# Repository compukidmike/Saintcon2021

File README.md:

# Saintcon2021

This year's badge was created by compukidmike, Professor_Plum, and Sodium_Hydrogen. It's styled after a combination lock and the shackle actually opens!

We tried something different for the front PCB. We used pcbbuy.com because they can do 2-color soldermask. It didn't turn out exactly like planned, but it was still a cool option that we'll probably use in the future.

One of the major features of the badge is NFC. The badge can read and write NFC tags, as well as emulate cards. This is used for sharing contact information, reading unlock tags, and trading items.

The main microcontroller is an ATSAME53J18A. The NFC controller is an ST25R95 and the LCD is actually round. The badge is composed of a stack of PCBs (4 boards thick, 5 boards total). Here's an exploded view of the badge:

One of the big challenges was fitting parts under the screen. We've got the thickness of 2 boards (3.2mm) to fit everything. The LCD is 2.2mm thick, so that leaves 1mm for components. This made it extremely difficult to find parts, especially with the chip shortages this year.

## Firmware

### Compiling

You'll need to install ~~Atmel~~ Microchip Studio to compile the firmware. Once it's compiled, you can flash it to the badge with an SWD programmer, or follow the directions below to use the USB bootloader.

### Making a UF2 File

When you've compiled the firmware, Microchip Studio will create a bunch of files (likely in the Debug folder inside your project folder). You want the .hex file. You'll need to use a tool called uf2conv.py from https://github.com/microsoft/uf2 (it's in the utils folder). This python script will convert your hex file into a UF2 file that you can use to program your badge. Here's an example command: python .\uf2conv.py .\flash.bin -c -o .\flash.uf2

### Flashing

To re-flash your badge there is a USB bootloader. To activate it, move the power switch to USB and hold the button on the right side of the badge when you connect it to your computer. The screen should show some hardware tests and then it will connect to your computer as a mass storage device. Simply copy the new UF2 firmware file to the badge.

### External SPI Flash

The badge has an 8MB SPI flash chip that stores all the images. It can be reprogrammed via the bootloader, but it's a bit cumbersome. You'll need to use the makeFlash.py script in the ExternalFlash folder to create a binary file from the images. NOTE: The images will be placed in the binary one after the other aligned to 1024 byte boundaries. If you change the images, you'll need to update the list of image locations in flash.h

Once you've got the binary file, you need to convert it to a hex file. This can be done with with bin2hex.py script in the ExternalFlash folder. Here's an example command: python .\bin2hex.py .\flash.bin .\flash.hex

Finally, you need to convert this hex file into a UF2 file that the bootloader can use to reprogram the SPI flash. When using the uf2conv.py script, you'll need to add an offset parameter so that the bootloader knows this data is for the SPI flash. Here's an example command: python .\uf2conv.py .\flash.bin -c -b 0x4000000 -o .\flash.uf2

NOTE: When copying a UF2 file that reprograms the SPI flash, the badge will send an erase command to the SPI flash. This can take a while (30-60 seconds) and you will see an activity indicator on the screen. If this process takes too long, your computer may timeout on copying the file (the badge will change from "erasing" to "writing", but the LED will be pulsing slowly instead of blinking rapidly). If this happens, simply reset the badge into bootloader mode and copy the file again. This time the SPI flash will be empty and the erase command will be quick.

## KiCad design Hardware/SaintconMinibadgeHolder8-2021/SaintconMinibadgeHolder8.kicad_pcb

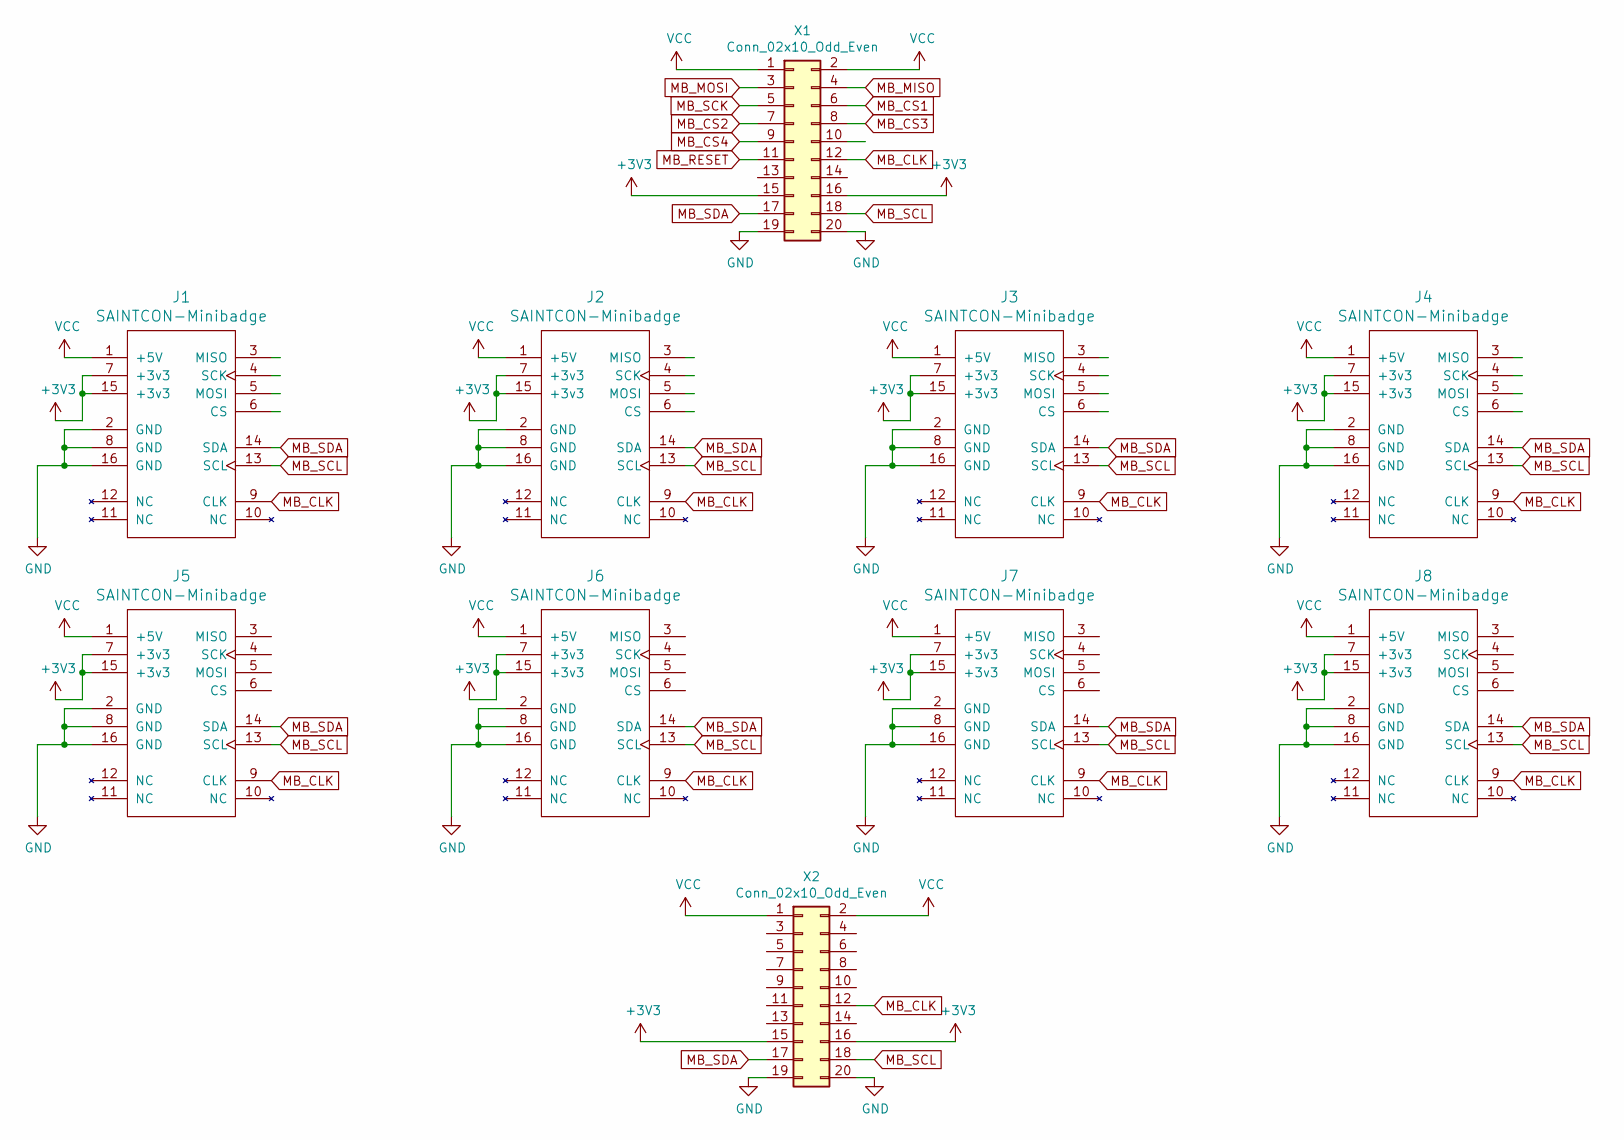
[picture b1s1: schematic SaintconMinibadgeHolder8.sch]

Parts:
J1, J2, J3, J4, J5, J6, J7, J8: SAINTCON-Minibadge; SAINTCON-Minibadge-Shiny
X1, X2: Conn_02x10_Odd_Even; Pin_Header_Straight_2x10_Pitch2.54mm

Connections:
+3V3: J1.7 (+3v3), J1.15 (+3v3), J2.7 (+3v3), J2.15 (+3v3), J3.7 (+3v3), J3.15 (+3v3), J4.7 (+3v3), J4.15 (+3v3), J5.7 (+3v3), J5.15 (+3v3), J6.7 (+3v3), J6.15 (+3v3), J7.7 (+3v3), J7.15 (+3v3), J8.7 (+3v3), J8.15 (+3v3), X1.15, X1.16, X2.15, X2.16
GND: J1.2 (GND), J1.8 (GND), J1.16 (GND), J2.2 (GND), J2.8 (GND), J2.16 (GND), J3.2 (GND), J3.8 (GND), J3.16 (GND), J4.2 (GND), J4.8 (GND), J4.16 (GND), J5.2 (GND), J5.8 (GND), J5.16 (GND), J6.2 (GND), J6.8 (GND), J6.16 (GND), J7.2 (GND), J7.8 (GND), J7.16 (GND), J8.2 (GND), J8.8 (GND), J8.16 (GND), X1.19, X1.20, X2.19, X2.20
MB_CLK: J1.9 (CLK), J2.9 (CLK), J3.9 (CLK), J4.9 (CLK), J5.9 (CLK), J6.9 (CLK), J7.9 (CLK), J8.9 (CLK), X1.12, X2.12
MB_CS1: X1.6
MB_CS2: X1.7
MB_CS3: X1.8
MB_CS4: X1.9
MB_MISO: X1.4
MB_MOSI: X1.3
MB_RESET: X1.11
MB_SCK: X1.5
MB_SCL: J1.13 (SCL), J2.13 (SCL), J3.13 (SCL), J4.13 (SCL), J5.13 (SCL), J6.13 (SCL), J7.13 (SCL), J8.13 (SCL), X1.18, X2.18
MB_SDA: J1.14 (SDA), J2.14 (SDA), J3.14 (SDA), J4.14 (SDA), J5.14 (SDA), J6.14 (SDA), J7.14 (SDA), J8.14 (SDA), X1.17, X2.17
VCC: J1.1 (+5V), J2.1 (+5V), J3.1 (+5V), J4.1 (+5V), J5.1 (+5V), J6.1 (+5V), J7.1 (+5V), J8.1 (+5V), X1.1, X1.2, X2.1, X2.2

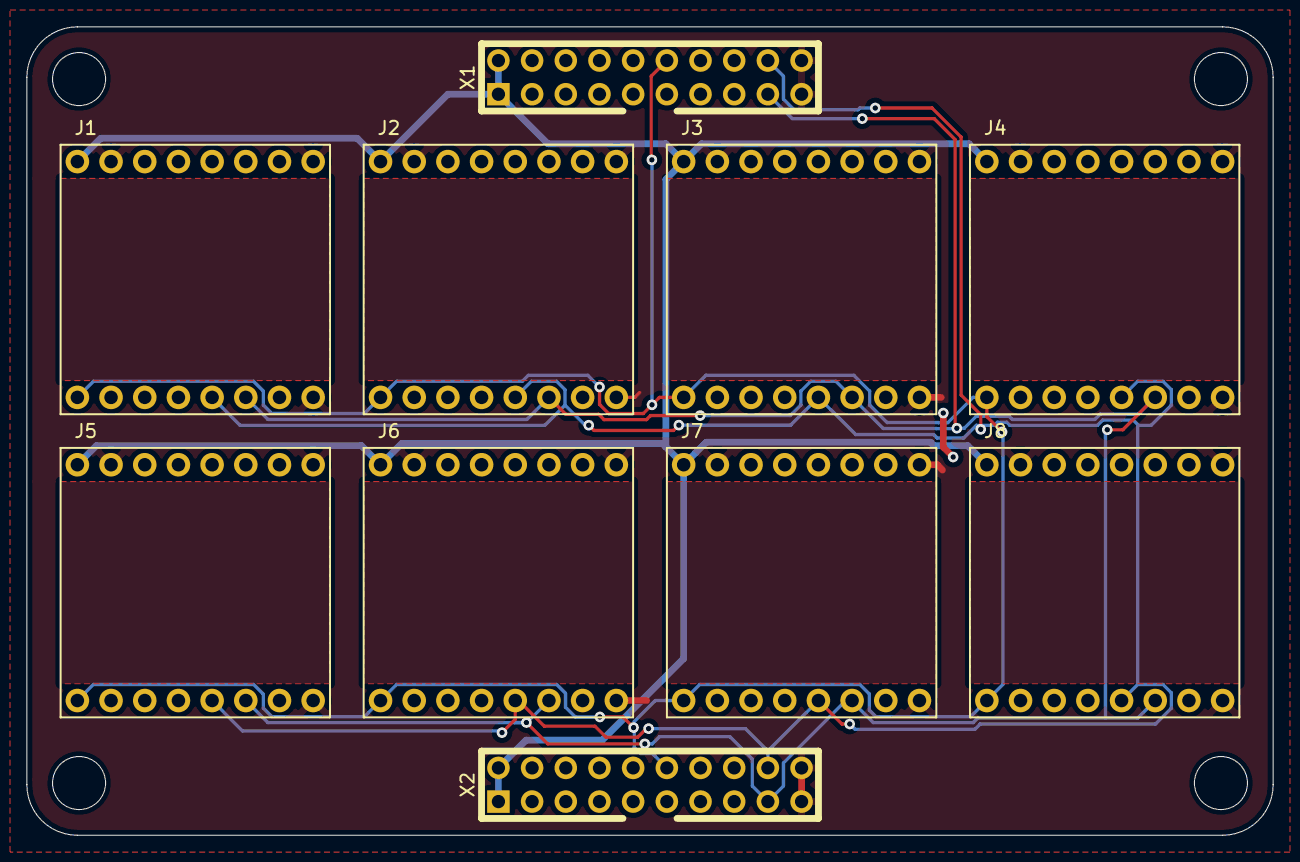
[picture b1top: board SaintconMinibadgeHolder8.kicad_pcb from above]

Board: 2 copper layers, 94.0 x 61.0 mm, 11 parts (1 on the bottom side), 6 nets.

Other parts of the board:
Ref**: Val**; SaintconLogo2021

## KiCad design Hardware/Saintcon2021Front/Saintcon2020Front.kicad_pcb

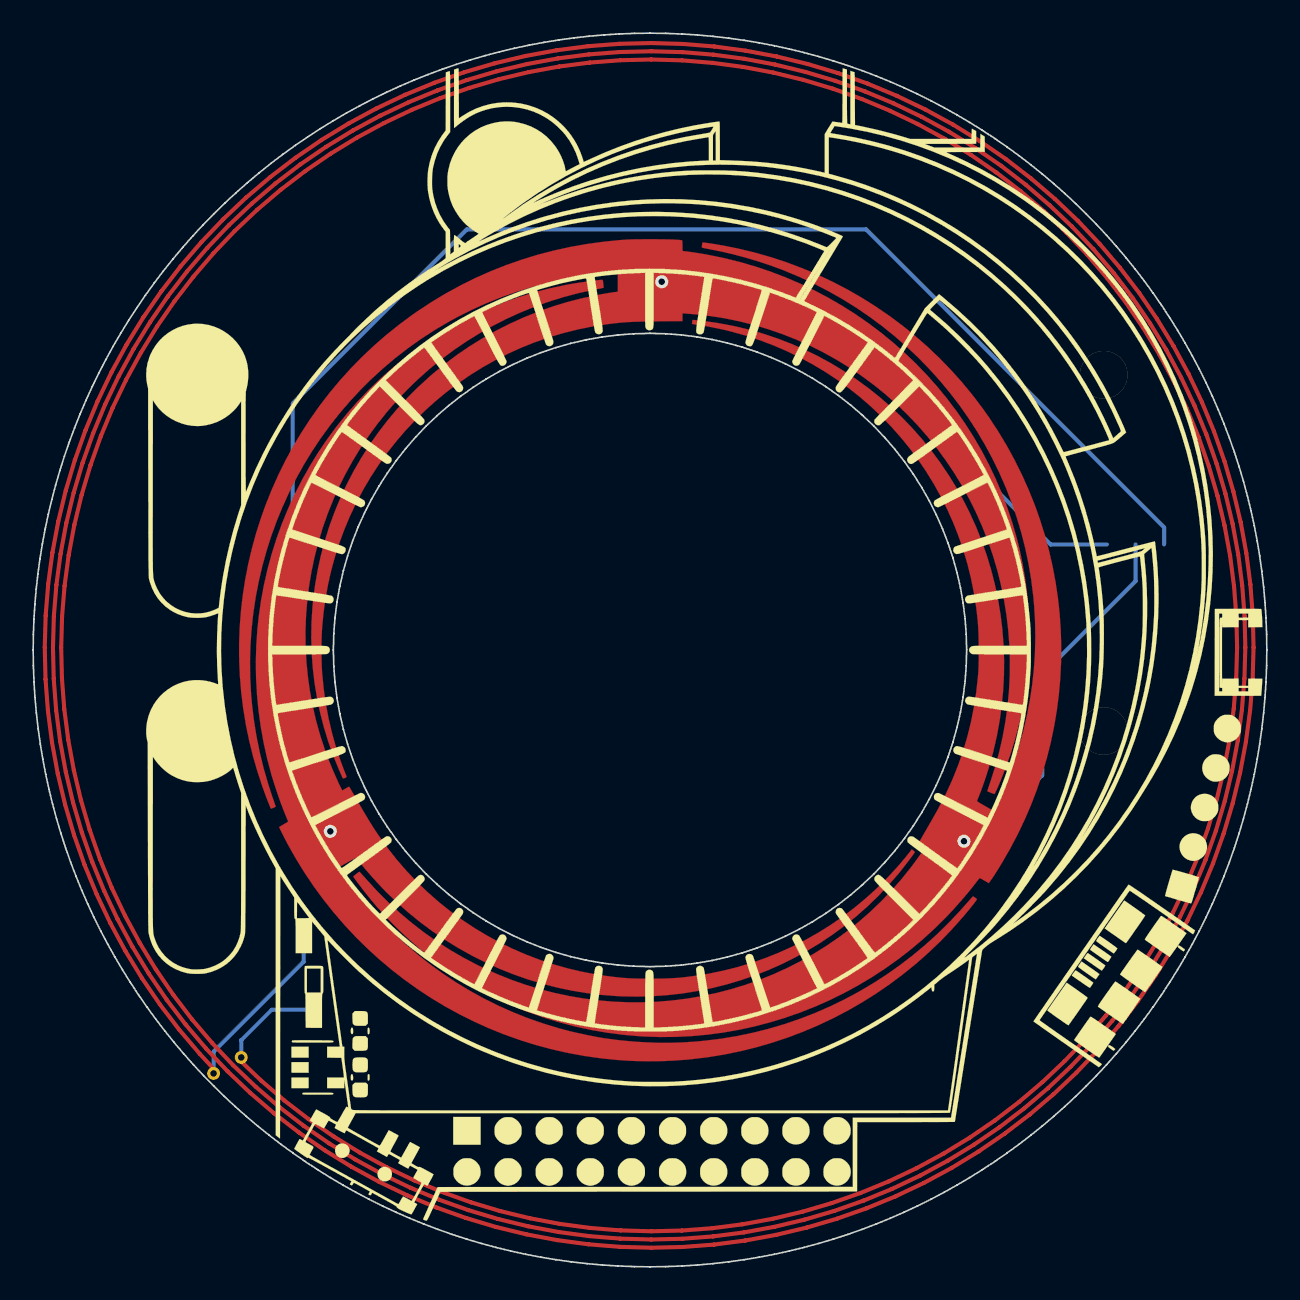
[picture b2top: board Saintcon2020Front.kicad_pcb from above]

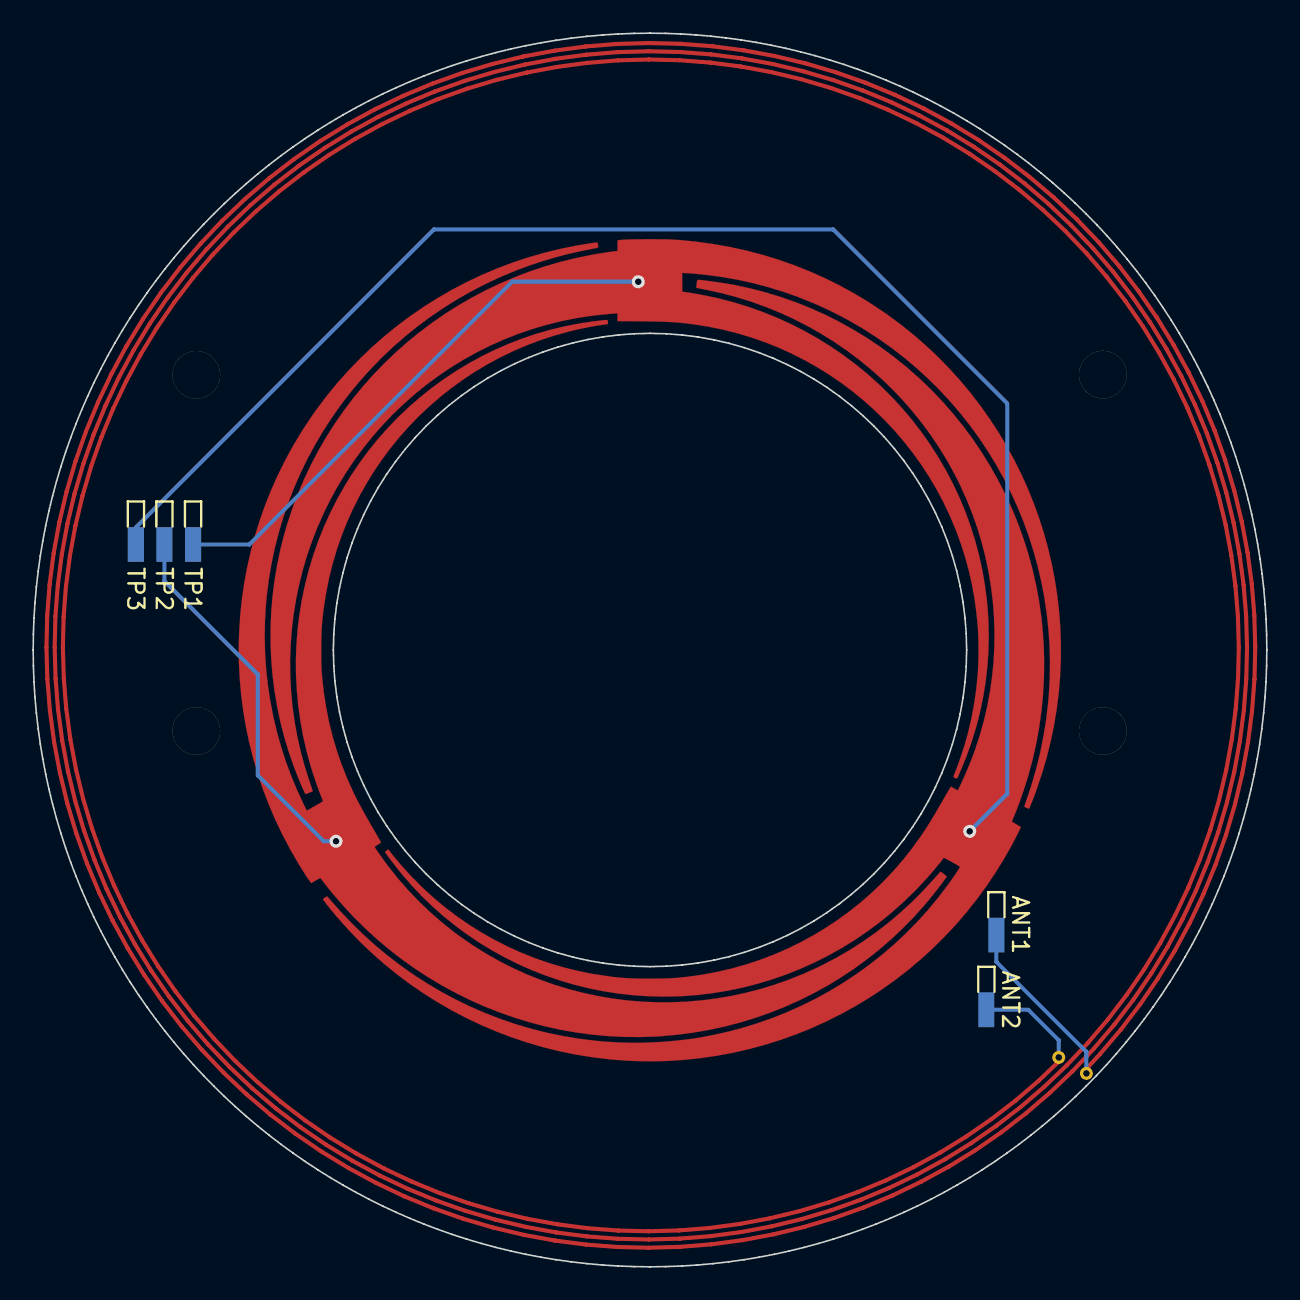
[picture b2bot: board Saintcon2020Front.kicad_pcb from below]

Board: 2 copper layers, 76.2 x 76.2 mm, 7 parts (5 on the bottom side), 2 nets.

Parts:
AE1: Antenna_Loop; SpiralAnt3_254000_508000
ANT1, ANT2: TestPoint; SPRING-120220-0315
Ref**: Val**; BoardFront3-Yellow
TP1, TP2, TP3: TestPoint; SPRING-120220-0315

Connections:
unnamed: AE1.1, ANT2.1
unnamed: AE1.2, ANT1.1

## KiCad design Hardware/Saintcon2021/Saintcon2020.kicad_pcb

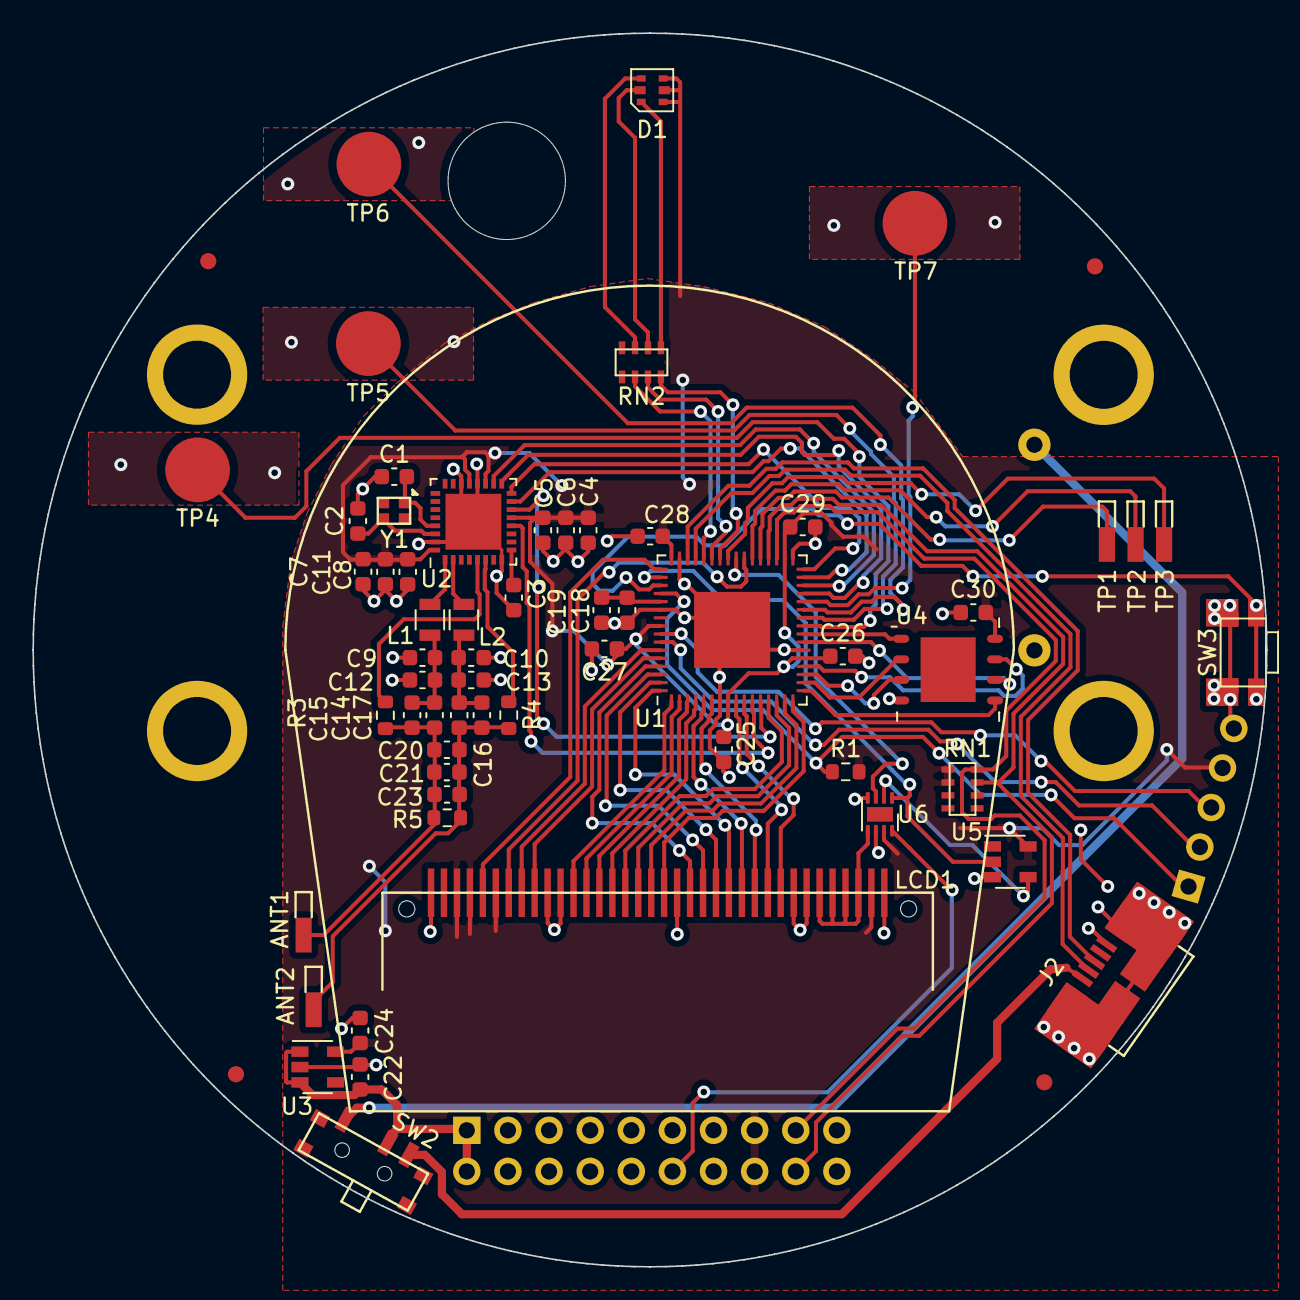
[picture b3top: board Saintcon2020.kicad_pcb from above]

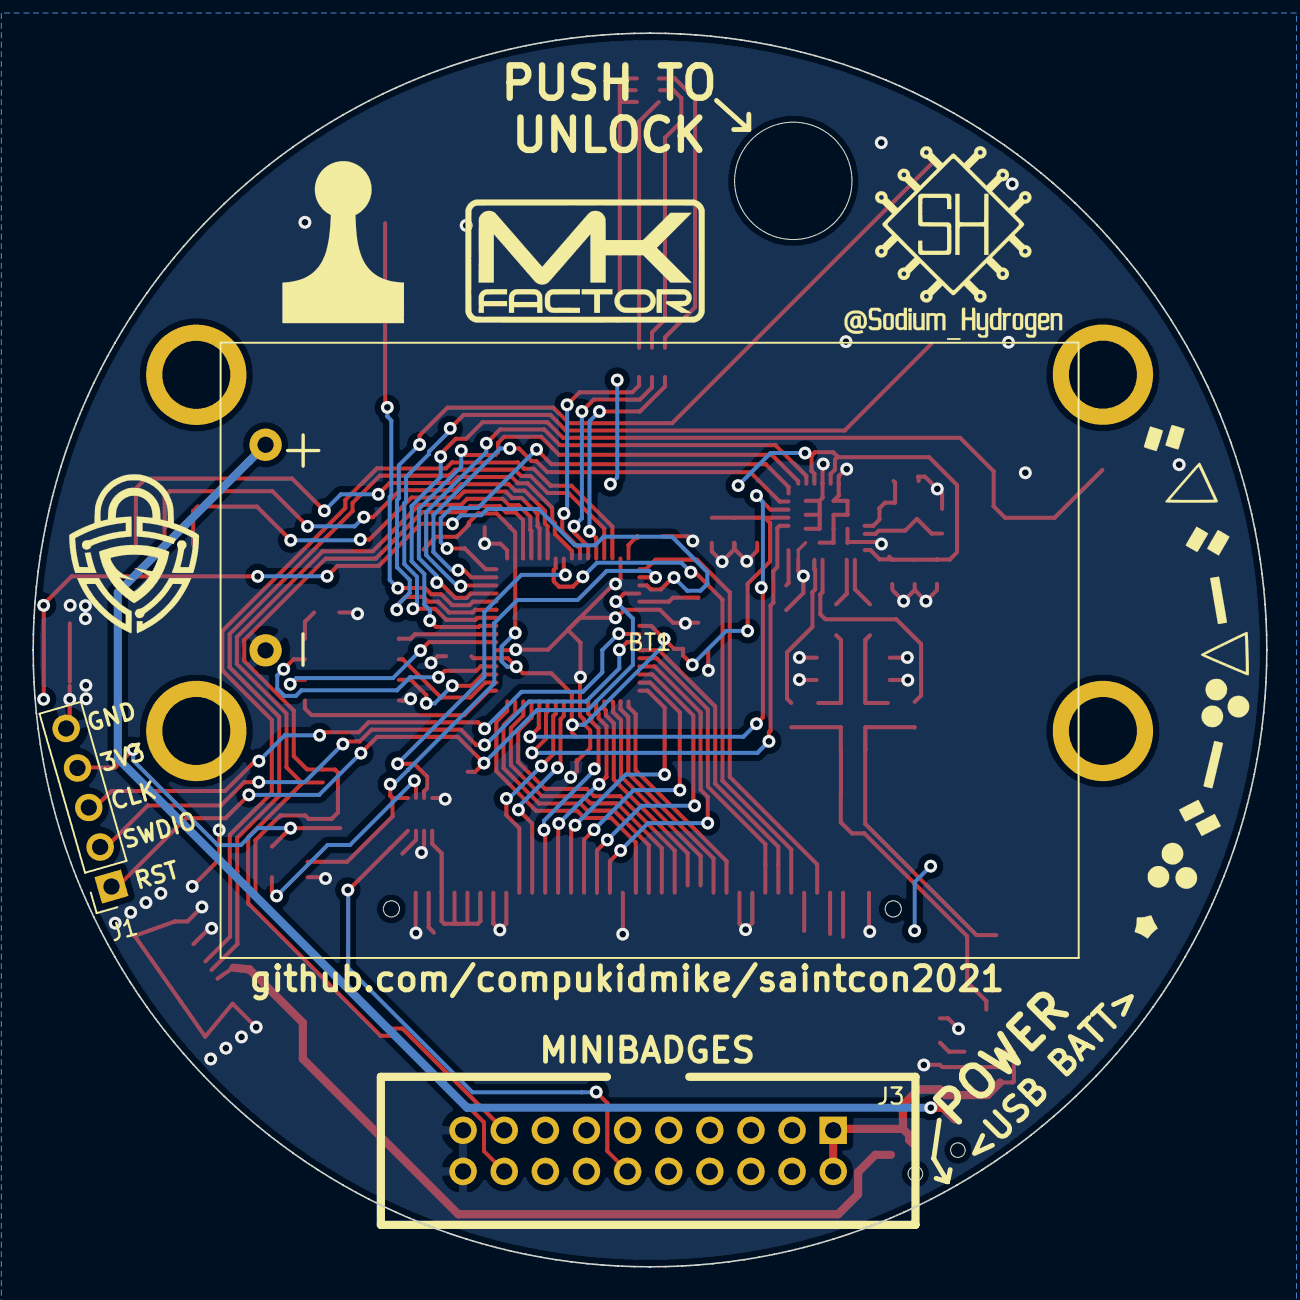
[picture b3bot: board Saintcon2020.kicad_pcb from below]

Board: 2 copper layers, 76.2 x 76.2 mm, 75 parts (6 on the bottom side), 75 nets.

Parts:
ANT1: NFC_ANT1; SPRING-120220-0315
ANT2: NFC_ANT2; SPRING-120220-0315
BT1: Battery; Battery3xAAA
C1, C2, C15, C16: 10pF; C_0603_1608Metric
C3: 1nF; C_0603_1608Metric
C4, C7: 1uF; C_0603_1608Metric
C5, C8: 0.01uF; C_0603_1608Metric
C6, C11, C18, C25, C26, C27, C28, C29, C30: 0.1uF; C_0603_1608Metric
C9, C10, C12, C13: 100pF; C_0603_1608Metric
C14, C17: 47pF; C_0603_1608Metric
C19, C22, C24: 4.7uF; C_0603_1608Metric
C20: 24pF; C_0603_1608Metric
C21, C23: DNP; C_0603_1608Metric
D1: 19-337C/RSBHGHC-A88/4T; 19-337C_RSBHGHC-A88_4T
FID1, FID2, FID3, FID4: Fiducial_1mm_Mask2mm
J1: Conn_01x05; PinSocket_1x05_P2.54mm_Vertical
J2: USB_B_Micro; 10118192-0002LF
J3: SBH11-PBPC-D10-ST-BK; Pin_Header_Straight_2x10_Pitch2.54mm
L1, L2: 560nH; L_0805
LCD1: RoundLCD; RoundLCD-36P
R1: 10k; R_0603_1608Metric
R3, R4: 330; R_0603_1608Metric
R5: DNP; R_0603_1608Metric
RN1, RN2: 1K; RAVF164D-RES_PACK_4
Ref**: Val**; SodiumHydrogen_logo
Ref**#2: Val**; SaintconLogo2021
Ref**#3: Val**; BackSilkCombo
Ref**#4: Val**; ProfessorPlum_logo
Ref**#5: Val**; BoardShape
STANDOFF1, STANDOFF2, STANDOFF3, STANDOFF4: Standoff-4-40
SW2: SW_SPDT; CUS-12B
SW3: SELECT; KMS231GFLS
TP1, TP2, TP3: TOUCH; SPRING-120220-0315
TP4, TP5, TP6: SHACKLE; TouchButton4mm
TP7: SHIM; TouchButton4mm
U1: ATSAME53J18A-M; QFN-64-1EP_9x9mm_P0.5mm_EP4.7x4.7mm
U2: ST25R95
U3: NCP115ASN330T2G; SOT-23-5
U4: AT25QF641B-MHB-T; UDFN-8_EP_6x5_Pitch1.27mm
U5: SN74LVC1G04DBVRG4; SOT-23-5
U6: A3910; DFN-8-1EP_2x2mm_P0.5mm_EP0.9x1.6mm
Y1: XRCGB27M120F3M10R0; Crystal-XRCGB27M120F3M10R0

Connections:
+3V3: C4.2, C5.2, C6.2, C7.2, C8.2, C11.2, C24.1, C25.1, C26.1, C27.1, C28.1, C29.1, C30.2, D1.2, D1.4, D1.6, J1.4, J3.15, J3.16, LCD1.2, LCD1.31, LCD1.33, LCD1.34, R1.2, RN1.7, RN1.8, U1.8, U1.21, U1.34, U1.48, U1.56, U2.13, U2.19, U2.21, U2.32, U3.5, U4.8, U5.5, U6.7
/D1: LCD1.25, U1.1
/D2: LCD1.24, U1.2
/D3: LCD1.23, U1.3
/D4: LCD1.22, U1.4
/D5: LCD1.21, U1.13
/D6: LCD1.20, U1.14
/D7: LCD1.19, U1.15
/D8: LCD1.18, U1.16
/D10: LCD1.16, U1.61
/D11: LCD1.15, U1.62
/D12: LCD1.14, U1.63
/D13: LCD1.13, U1.64
/D14: LCD1.12, U1.5
/D15: LCD1.11, U1.6
/D16: LCD1.10, U1.9
/D17: LCD1.9, U1.10
D+: J2.3, U1.46
D-: J2.2, U1.45
GND: BT1.2, C1.2, C2.2, C3.1, C4.1, C5.1, C6.1, C7.1, C8.1, C9.2, C10.1, C11.1, C12.2, C13.1, C18.2, C19.2, C22.2, C24.2, C25.2, C26.2, C27.2, C28.2, C29.2, C30.1, J1.5, J2.5, J2.6, J3.19, J3.20, LCD1.1, LCD1.7, LCD1.8, LCD1.17, LCD1.26, LCD1.27, LCD1.36, SW3.1, U1.7, U1.22, U1.33, U1.47, U1.54, U1.65, U2.8, U2.20, U2.22, U2.31, U2.33, U3.2, U4.4, U5.3, U6.4, U6.6
LCD_BL: LCD1.3, LCD1.4, LCD1.5, LCD1.6, U6.5
LCD_BL_CTRL: U1.40, U6.3
LCD_CS: LCD1.28, U1.60
LCD_RS: LCD1.29, U1.59
LCD_RST: LCD1.32, U1.49
LCD_WR: LCD1.30, U1.39
LEDB: RN2.3, U1.44
LEDG: RN2.2, U1.43
LEDR: RN2.1, U1.42
MB_CLK: J3.12, U6.8
MB_CLK_CTRL: U1.50, U5.2, U6.1
MB_SCL: J3.18, RN1.2, U1.36
MB_SDA: J3.17, RN1.1, U1.35
NFC_CS: U1.31, U2.15
NFC_IRQ_IN: U1.11, U2.12
NFC_IRQ_OUT: U1.12, U2.14
NFC_MISO: U1.32, U2.16
NFC_MOSI: U1.29, U2.17
NFC_SCK: U1.30, U2.18
unnamed: ANT1.1, C14.1, C15.1, C20.1, C21.1, C23.1, R3.1, R5.1
unnamed: ANT2.1, C16.1, C17.1, C20.2, C21.2, C23.2, R4.1, R5.2
unnamed: BT1.1, SW2.1
unnamed: C1.1, U2.29, Y1.1
unnamed: C2.1, U2.30, Y1.3
unnamed: C3.2, U2.9
unnamed: C10.2, C13.2, C16.2, C17.2, L2.2
unnamed: C9.1, C12.1, C14.2, C15.2, L1.2
unnamed: C18.1, C19.1, U1.53
unnamed: D1.1, RN2.8
unnamed: D1.3, RN2.7
unnamed: D1.5, RN2.6
unnamed: J2.1, SW2.3
unnamed: L1.1, U2.1
unnamed: L2.1, U2.2
unnamed: R3.2, U2.5
unnamed: R4.2, U2.6
unnamed: SW3.2, U1.51
unnamed: TP1.1, U1.37
unnamed: TP2.1, U1.38
unnamed: TP3.1, U1.41
unnamed: TP4.1, U1.25
unnamed: TP5.1, U1.26
unnamed: TP6.1, U1.27
unnamed: TP7.1, U1.28
unnamed: U5.4, U6.2
QSPI_CLK: U1.23, U4.6
QSPI_CS: U1.24, U4.1
QSPI_IO0: U1.17, U4.5
QSPI_IO1: U1.18, U4.2
QSPI_IO2: U1.19, U4.3
QSPI_IO3: U1.20, U4.7
RESET: J1.1, R1.1, U1.52
SWDCLK: J1.3, U1.57
SWDIO: J1.2, U1.58
VCC: C22.1, J3.1, J3.2, SW2.2, U3.1, U3.3

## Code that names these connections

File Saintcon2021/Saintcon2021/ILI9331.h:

/*
 * ILI9331.h
 *
 * Created: 8/16/2021 9:43:16 AM
 *  Author: Professor Plum
 */ 


#ifndef ILI9331_H_
#define ILI9331_H_

#define LCD_WR	16
#define LCD_CS	31
#define LCD_RS	30
#define LCD_BL	17
#define LCD_RST 22

#define RGB(r, g, b) ((((r) & 0xF8) << 8) | (((g) & 0xFC) << 3) | ((b) >> 3))

void LCD_DrawPixel(uint8_t x, uint8_t y, uint16_t color);
void LCD_DrawImage(int x, int y, int w, int h, uint16_t *data);
void LCD_FillRect(int x, int y, int w, int h, uint16_t color);
void LCD_DrawLine (int x0, int y0, int x1, int y1, uint16_t color);
void LCD_Init();
void LCD_Reset();
void LCD_Sleep();
void LCD_Wake();


#endif /* ILI9331_H_ */

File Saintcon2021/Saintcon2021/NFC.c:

#include "nfc.h"
#include "main.h"
#include "string.h"
#include "platform.h"
#include <stdlib.h>

bool nfc_init(void){
	
	spi_m_sync_get_io_descriptor(&SPI_1, &io);

	spi_m_sync_enable(&SPI_1);

	gpio_set_pin_direction(NFC_CS_PIN, GPIO_DIRECTION_OUT);
	gpio_set_pin_direction(NFC_IRQ_IN_PIN, GPIO_DIRECTION_OUT);
	gpio_set_pin_direction(NFC_IRQ_OUT_PIN,GPIO_DIRECTION_IN);
	gpio_set_pin_pull_mode(NFC_IRQ_OUT_PIN,GPIO_PULL_UP);
	gpio_set_pin_level(NFC_CS_PIN, true);
	gpio_set_pin_level(NFC_IRQ_IN_PIN, true);
	
	nfc_reset();

	delay_ms(2); //Occasionally hangs without a delay here. Might be able to shorten it.
// 	delay_ms(0.2);
	gpio_set_pin_level(NFC_IRQ_IN_PIN, false);
// 	delay_ms(0.2);
	gpio_set_pin_level(NFC_IRQ_IN_PIN, true);
	delay_ms(20);

	nfc_test();
	
	uint8_t rxbuff[20] = {};
	uint8_t txbuff[20] = {};
	uint8_t size;	bool validFrame = false;
	
	while(!validFrame){ 
		size = nfc_comm(rxbuff, txbuff, "\x00\x02\x02\x12\x08", 5);
		
		size = nfc_comm(rxbuff, txbuff, "\x00\x05\x00", 3);

		if(size == 0){			nfc_poll();			size = nfc_read(rxbuff);			char data[2] = {0};			itoa(rxbuff[1],data,16);			platformLog(data);			if(rxbuff[1] == 0x80) validFrame = true;		}	}	while(1);	
}

void nfc_poll(){

	uint8_t rbuff = 0;
	uint8_t tbuff = 3;
	gpio_set_pin_level(NFC_CS_PIN, false);
	while( (rbuff & 0xf8) != 8){
		delay_ms(1);
		spi_m_sync_io_readwrite(io, &rbuff, &tbuff, 1);	
	}
	gpio_set_pin_level(NFC_CS_PIN, true);
}

bool nfc_test(){
	uint8_t rxbuff[20] = {0};
	uint8_t txbuff[3] = {};
			
	uint8_t size = nfc_comm(rxbuff, txbuff, "\x00\x01\x00", 3);
	
	if (size == 15){
		platformLog((char*)rxbuff+3);
		return true;
	}
	return false;
	
}

uint8_t nfc_read(uint8_t* rxbuff){
	uint8_t txbuff[3] = {2};
	uint8_t size = 0;
	uint8_t buff = 0;
	
	gpio_set_pin_level(NFC_CS_PIN, false);
	spi_m_sync_io_readwrite(io, rxbuff, txbuff, 3);
	if(rxbuff[1] == 0){
		size = rxbuff[2];
		for(uint8_t i = 0; i < size; i++){
			spi_m_sync_io_readwrite(io, &buff, txbuff, 1);
			rxbuff[3+i] = buff;
		}
	}
	gpio_set_pin_level(NFC_CS_PIN, true);
	return size;
}

void nfc_reset(){
	uint8_t tx[2] = {};
	uint8_t buff[2] = {};
	
 	memcpy(tx, "\x00\x55", 2);
 	gpio_set_pin_level(NFC_CS_PIN, false);
 	spi_m_sync_io_readwrite(io, buff, tx, 2);
 	gpio_set_pin_level(NFC_CS_PIN, true);
	
	memcpy(tx, "\x01", 1);
	gpio_set_pin_level(NFC_CS_PIN, false);
	spi_m_sync_io_readwrite(io, buff, tx, 1);
	gpio_set_pin_level(NFC_CS_PIN, true);
	
}

uint8_t nfc_comm(uint8_t * rx, uint8_t * tx, char * command, uint8_t size){
	memcpy(tx, command, size);
	gpio_set_pin_level(NFC_CS_PIN, false);
	spi_m_sync_io_readwrite(io, rx, tx, size);
	gpio_set_pin_level(NFC_CS_PIN, true);
	
	nfc_poll();
	
	return nfc_read(rx);	
}

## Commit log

2021-08-17 Base Project Code
2021-08-17 Added Basic LCD driver (still needs DMA), added some files to ignore list
2021-08-18 Added FrameBuffer
2021-08-19 Add Touch Wheel
2021-08-19 Touch Test Code
2021-08-19 Fix abs implicit declaration with proper include
2021-08-19 Added QSPI flash support
2021-08-20 Add EEPROM emulator driver
2021-08-23 User interface work, depends on flash image, milis timer, and other features not done yet
2021-08-23 LCD speed improvments
2021-08-24 Changed button to use interrupts
2021-08-26 Added USB CDC driver
2021-08-29 Added flash imaging code, fixed image rotation code
2021-08-30 Moved touch_process to timer interrupt for better responsiveness
2021-08-31 Combo scene improvements
2021-09-05 Basic NFC Code
    NFC can detect tags
2021-09-05 NFC and millis fixes
    fix merge issues and fix millis adding when returning value.
2021-09-05 Fix LED PWM driver
2021-09-10 Updated Flash driver for new chip
2021-09-11 Add touch buttons for shackle
2021-09-11 Fix touch button code
2021-09-12 Added menu screen are
2021-09-12 Fixe broken merge
2021-09-12 starting nfc
2021-09-12 Added NFC feild detection
2021-09-12 adjusted combo detection, adding more menu art
2021-09-13 Finished menu screen art
2021-09-13 Change touch wheel calibration
2021-09-14 Cleanup nfc
2021-09-14 Bug fixes
2021-09-14 rename nfc.c
2021-09-14 NFC fixes
    Ignore field errors and wait for valid frame.
2021-09-14 Fix merge
2021-09-14 Speed improvments to menu screen
2021-09-14 Shaved 7ms off blt time
2021-09-17 Added rewards and message screens. Improved combo user input
2021-09-18 Change USB Vendor ID
    Using the default Atmel vendor ID causes the IDE to think it's a dev board which makes debugging slow.
2021-09-18 Added true RNG
2021-09-19 Replacing rand with TRNG in Rouge game
2021-09-19 Added AES modules
2021-09-19 Turn off display when not in use to save power
2021-09-24 Added NFC scene, build art, inventory art, and progress on build scene
2021-09-25 Finished build Scene, updated pixel art with new SC logo
2021-09-25 Added SHA1 hash support
2021-09-26 NFC work
2021-09-26 Cleanup code
2021-09-27 Added cyber tunnel game
2021-10-04 NFC Tag Emulation
    Very crude test code to do tag emulation with an NDEF record that points to saintcon.org
2021-10-05 Update tag emulation
2021-10-05 Added VCARD support
2021-10-05 Add population of first 3 nfc pages
2021-10-05 Activate Vcard
2021-10-05 Fix off by 1 error with page addressing
2021-10-05 Added more tag registers
2021-10-06 NFC Fixes - Reading NDEF records from Type 2 tags
2021-10-06 Incramental
2021-10-06 More reader functionality
2021-10-08 Clean up nfc code base some more
2021-10-09 Added trade Scene
2021-10-11 Added rewards for badge achievments
2021-10-11 Added basic minibadge detection
2021-10-11 Work on inturrupts
2021-10-11 NFC Works and restarts!!
2021-10-13 Added missing files, eeprom fix, and more functions in prep for nfc ssupport
2021-10-13 NFC writing support
2021-10-13 Add tag writing mode
2021-10-13 Proper NFC end write detection
2021-10-14 Hooking in NFC functions
2021-10-14 Working on nfc
2021-10-14 Added minibadge message scrollinf support
2021-10-14 Clean up old files
2021-10-15 Bootloader
    Add bootloader code, adjust flash offset for main program.
2021-10-15 fixed build
2021-10-15 Fixed Badge crash with NFC IRQ
2021-10-15 Fix read timings to match ntag2xx standars (5ms max)
2021-10-15 added more nfc hashes and work on trading
2021-10-15 Maybe get nfc writer working. Also change links to sched
2021-10-15 typo
2021-10-15 Finished badge trading
2021-10-15 Fix Touch Wheel Linearity
2021-10-15 Added read checks, changed to release build
2021-10-15 fixed bug where build doesn't save
2021-10-16 Fix tag emu bug, Clasp dect bug, enable jail
2021-10-16 Fixed cheating guards in rouge game
2021-10-16 Added more lights, fixed nfc tag rewards bug
2021-10-16 Minor bugs fixes and improvments
2021-10-16 Added more quotes
2021-10-16 Remove flash test code
2021-10-16 fixing trading bugs
2021-10-16 More bug fixes
2021-10-16 Fix flash partial erase
2021-10-16 added more light status and eprom erase info
2021-10-17 Add Minibadge CLK, fix NFC unlocks, fix bootloader available size, replace bird image with saintcon logo
2021-10-18 Fix off by one error
2021-10-19 fix flash erase for real this time
2021-10-26 Add Hardware files (schematic, kicad files, etc)
2021-11-12 Fixed minibadge message collision
2023-04-06 Add minibadge holder board
